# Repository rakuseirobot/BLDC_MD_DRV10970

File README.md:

View this project on [CADLAB.io](https://cadlab.io/project/23111). 

# BLDC_MD_DRV10970
Motor driver for BLDC with hall sensors using DRV10970(Texas Instruments)

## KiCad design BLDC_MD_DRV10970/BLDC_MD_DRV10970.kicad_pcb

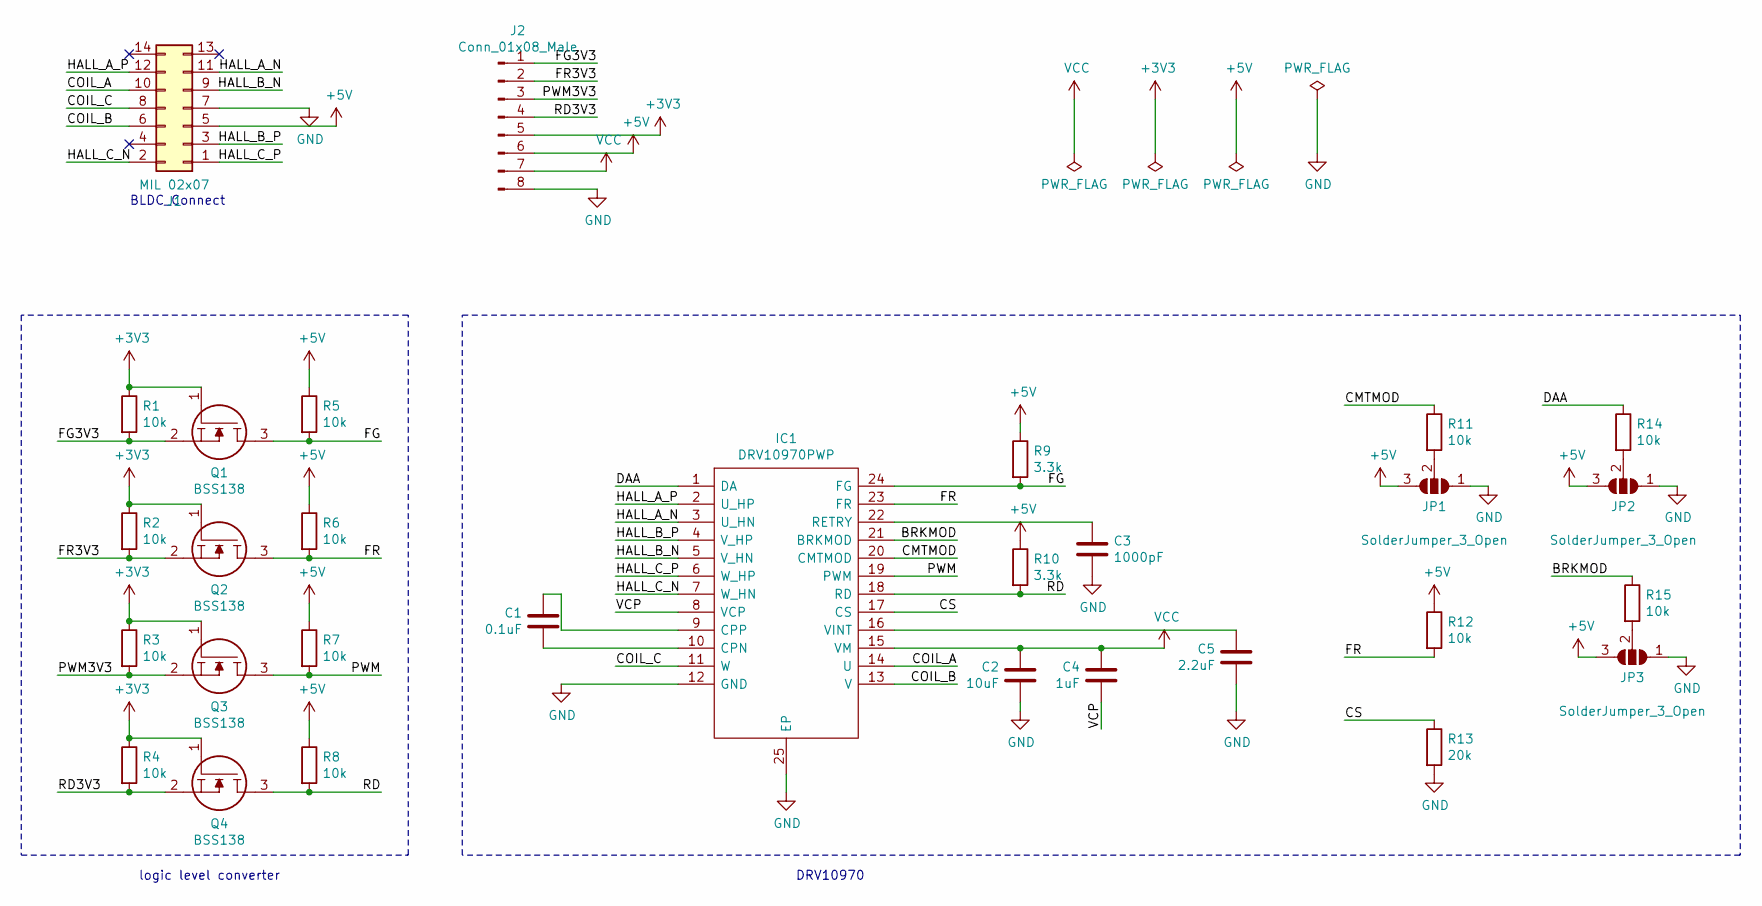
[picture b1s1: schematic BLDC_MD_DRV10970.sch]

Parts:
C1: 0.1uF; C_0603_1608Metric
C2: 10uF; C_0603_1608Metric
C3: 1000pF; C_0603_1608Metric
C4: 1uF; C_0603_1608Metric
C5: 2.2uF; C_0603_1608Metric
IC1: DRV10970PWP; SOP65P640X120-25N; Manufacturer_Part_Number DRV10970PWP; Mouser Part Number 595-DRV10970PWP
J1: MIL 02x07; PinHeader_2x07_P2.54mm_Horizontal
J2: Conn_01x08_Male; PinHeader_1x08_P2.54mm_Horizontal
JP1, JP2, JP3: SolderJumper_3_Open; SolderJumper-3_P2.0mm_Open_TrianglePad1.0x1.5mm
Q1, Q2, Q3, Q4: BSS138; SOT95P240X120-3N; Manufacturer_Part_Number BSS138; Mouser Part Number 512-BSS138
R1, R2, R3, R4, R5, R6, R7, R8, R11, R12, R14, R15: 10k; R_0603_1608Metric
R9, R10: 3.3k; R_0603_1608Metric
R13: 20k; R_0603_1608Metric

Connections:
+3V3: J2.5, Q1.1, Q2.1, Q3.1, Q4.1, R1.1, R2.1, R3.1, R4.1
+5V: J1.5, J2.6, JP1.3 (B), JP2.3 (B), JP3.3 (B), R5.1, R6.1, R7.1, R8.1, R9.1, R10.1, R12.1
/BRKMOD: IC1.21 (BRKMOD), R15.1
/CMTMOD: IC1.20 (CMTMOD), R11.1
/COIL_A: IC1.14 (U), J1.10
/COIL_B: IC1.13 (V), J1.6
/COIL_C: IC1.11 (W), J1.8
/CS: IC1.17 (CS), R13.1
/DAA: IC1.1 (DA), R14.1
/FG: IC1.24 (FG), Q1.3, R5.2, R9.2
/FG3V3: J2.1, Q1.2, R1.2
/FR: IC1.23 (FR), Q2.3, R6.2, R12.2
/FR3V3: J2.2, Q2.2, R2.2
/HALL_A_N: IC1.3 (U_HN), J1.11
/HALL_A_P: IC1.2 (U_HP), J1.12
/HALL_B_N: IC1.5 (V_HN), J1.9
/HALL_B_P: IC1.4 (V_HP), J1.3
/HALL_C_N: IC1.7 (W_HN), J1.2
/HALL_C_P: IC1.6 (W_HP), J1.1
/PWM: IC1.19 (PWM), Q3.3, R7.2
/PWM3V3: J2.3, Q3.2, R3.2
/RD: IC1.18 (RD), Q4.3, R8.2, R10.2
/RD3V3: J2.4, Q4.2, R4.2
/VCP: C4.1, IC1.8 (VCP)
GND: C2.1, C3.2, C5.1, IC1.12 (GND), IC1.25 (EP), J1.7, J2.8, JP1.1 (A), JP2.1 (A), JP3.1 (A), R13.2
unnamed: C1.1, IC1.10 (CPN)
unnamed: C1.2, IC1.9 (CPP)
unnamed: C3.1, IC1.22 (RETRY)
unnamed: C5.2, IC1.16 (VINT)
unnamed: JP1.2 (C), R11.2
unnamed: JP2.2 (C), R14.2
unnamed: JP3.2 (C), R15.2
VCC: C2.2, C4.2, IC1.15 (VM), J2.7

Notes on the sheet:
BLDC_Connect
logic level converter
DRV10970

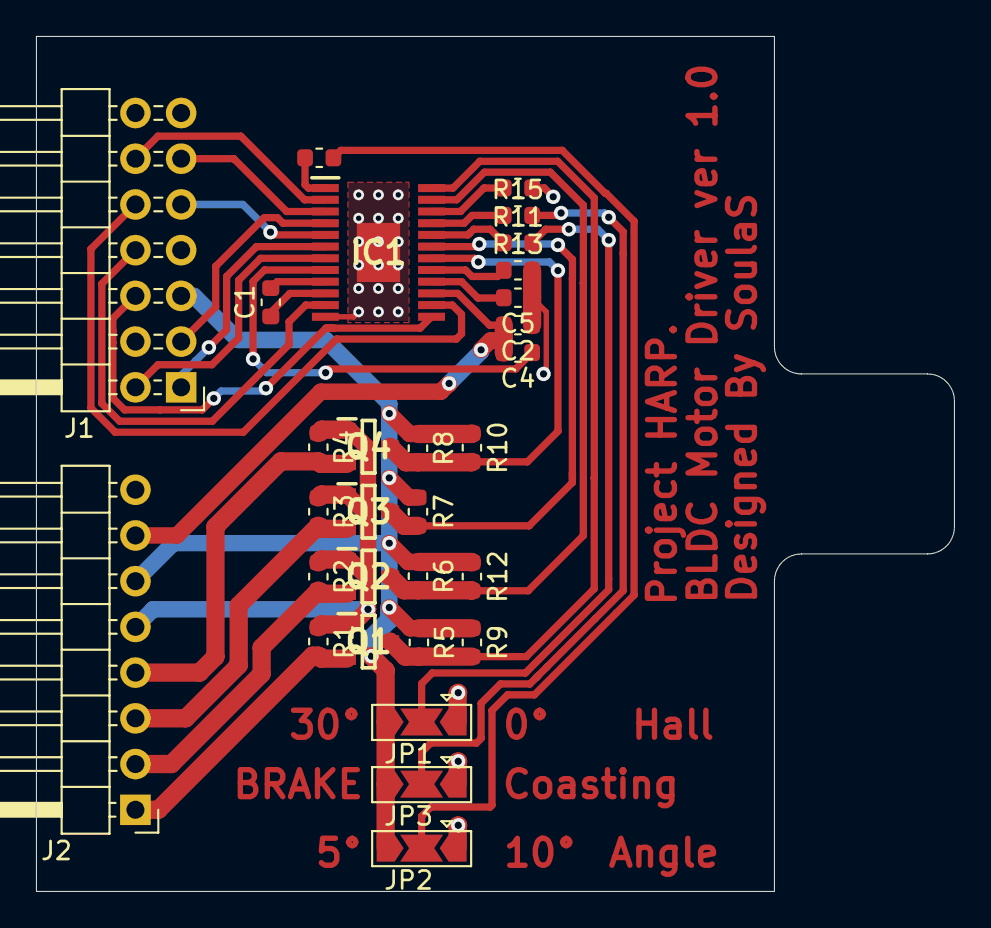
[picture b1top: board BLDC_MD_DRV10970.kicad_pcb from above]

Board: 2 copper layers, 51.0 x 47.5 mm, 30 parts (0 on the bottom side), 33 nets.

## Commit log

2020-07-16 Backlink to CADLAB.io has been added.
2020-07-16 Created kicad project and initialized
2020-07-16 Placed connector for BLDC
2020-07-16 changed BLDC port from 12pin to 14pin connector, some pins will NOT be used.
2020-07-16 changed BLDC_Connector type. from 02x06 to 02x07
2020-07-17 done drowing schema.
2020-07-18 Related symbol and footprint
2020-07-18 set up design rules
2020-07-18 routed all connections and exported board 3d files
2020-07-18 added picture from bottom side.
2020-07-18 fixed letter mistakes.
2020-07-18 added reference image file for readme.md
2020-08-11 added gerber files for production for elecrow
2020-08-17 Added BOM file
